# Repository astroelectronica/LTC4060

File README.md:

# LTC4060
Standalone Linear NiMH/NiCd Fast Battery Charger

AE01012060

https://www.analog.com/en/products/ltc4060.html

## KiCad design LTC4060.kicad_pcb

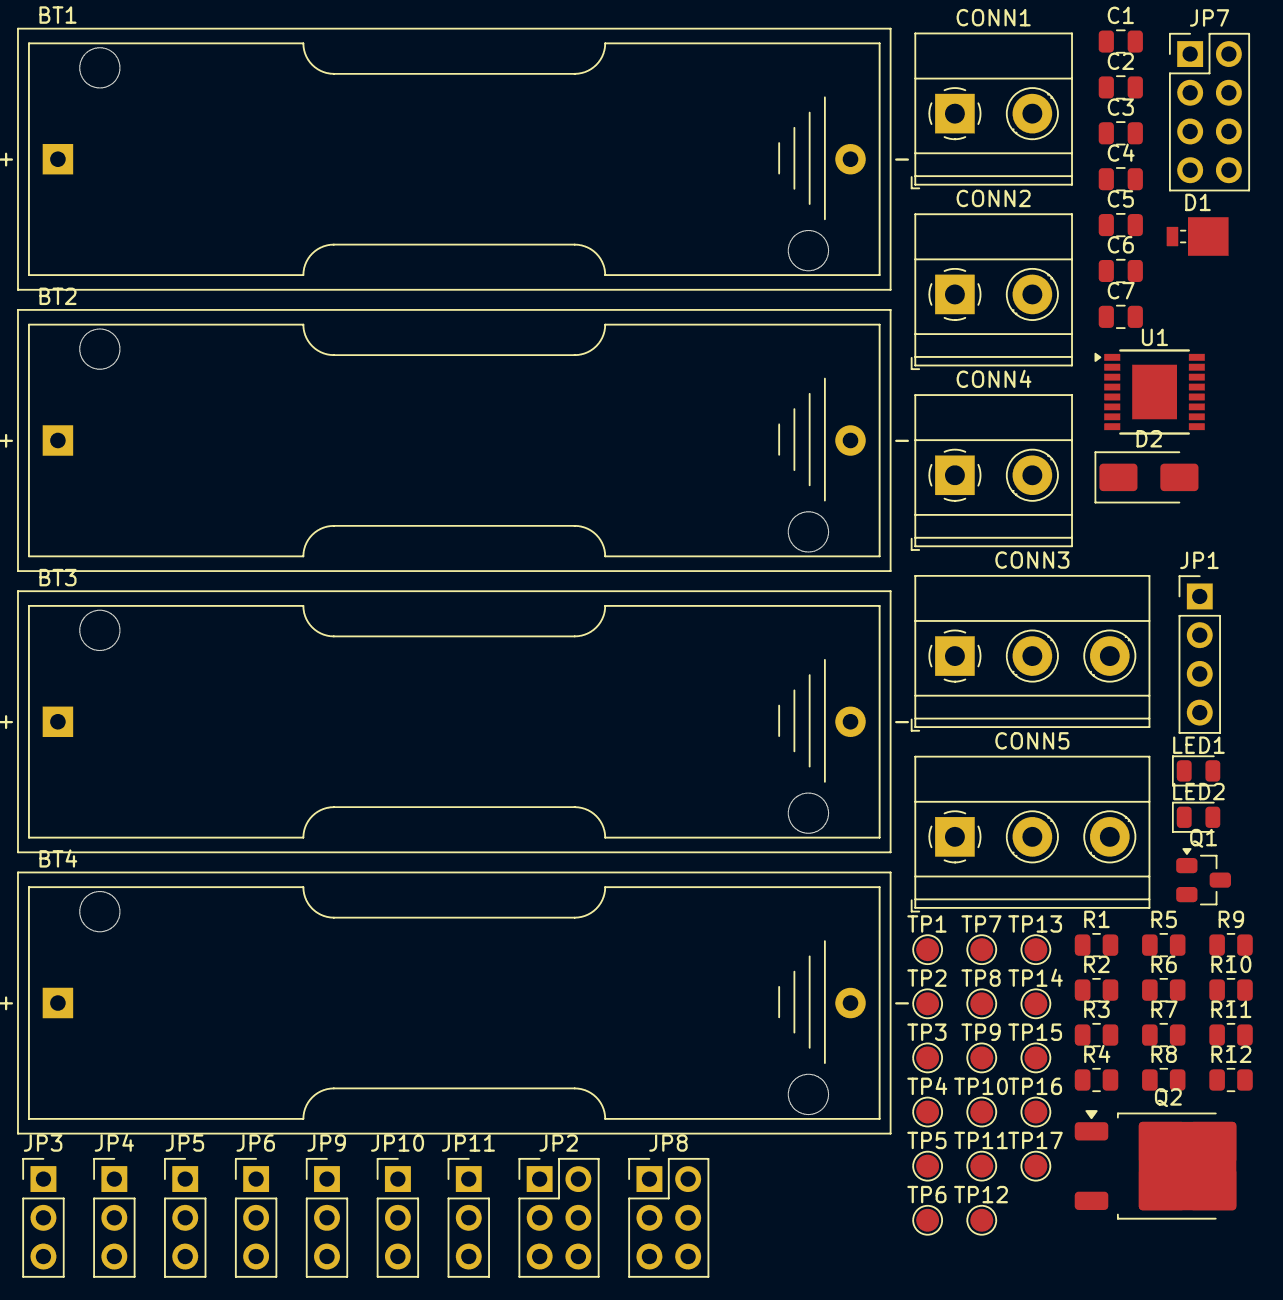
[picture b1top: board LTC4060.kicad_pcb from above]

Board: 2 copper layers, 63 parts (0 on the bottom side), 37 nets, no tracks yet.

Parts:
BT1: CELL1; BatteryHolder_Keystone_2460_1xAA
BT2: CELL2; BatteryHolder_Keystone_2460_1xAA
BT3: CELL3; BatteryHolder_Keystone_2460_1xAA
BT4: CELL4; BatteryHolder_Keystone_2460_1xAA
C1: 1uF; C_0805_2012Metric
C2: 10uF; C_0805_2012Metric
C3: 220pF; C_0805_2012Metric
C4: 150pF; C_0805_2012Metric
C5: 470pF; C_0805_2012Metric
C6: 1200pF; C_0805_2012Metric
C7: 2700pF; C_0805_2012Metric
CONN1: NTC; TerminalBlock_Phoenix_MKDS-1,5-2-5.08_1x02_P5.08mm_Horizont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
CONN2: VIN; TerminalBlock_Phoenix_MKDS-1,5-2-5.08_1x02_P5.08mm_Horizont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
CONN3: TIMER_PROG_EXT; TerminalBlock_Phoenix_MKDS-1,5-3-5.08_1x03_P5.08mm_Horizont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
CONN4: SYST_LOAD; TerminalBlock_Phoenix_MKDS-1,5-2-5.08_1x02_P5.08mm_Horizont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
CONN5: EXT_PNP; TerminalBlock_Phoenix_MKDS-1,5-3-5.08_1x03_P5.08mm_Horizont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
D1: MBRM120LT3; D_Powermite_KA
D2: B220A; D_SMA
JP1: CHRG_CURRENT; PinHeader_1x04_P2.54mm_Vertical
JP2: RECHARGE; PinHeader_2x03_P2.54mm_Vertical
JP3: NTC; PinHeader_1x03_P2.54mm_Vertical
JP4: SEL1; PinHeader_1x03_P2.54mm_Vertical
JP5: SEL0; PinHeader_1x03_P2.54mm_Vertical
JP6: CHEM; PinHeader_1x03_P2.54mm_Vertical
JP7: TIMER; PinHeader_2x04_P2.54mm_Vertical
JP8: EXT_PNP; PinHeader_2x03_P2.54mm_Vertical
JP9: SEL2; PinHeader_1x03_P2.54mm_Vertical
JP10: SEL3; PinHeader_1x03_P2.54mm_Vertical
JP11: SEL4; PinHeader_1x03_P2.54mm_Vertical
LED1: CHRG; LED_0805_2012Metric
LED2: ACPR; LED_0805_2012Metric
Q1: FDN306P; SuperSOT-3
Q2: MJD210T4G; TO-252-2
R1: 931R; R_0805_2012Metric
R2: 2.8K; R_0805_2012Metric
R3, R12: 1R; R_0805_2012Metric
R4: 576R; R_0805_2012Metric
R5: 2.21K; R_0805_2012Metric
R6: 4.42K; R_0805_2012Metric
R7: 68K; R_0805_2012Metric
R8, R10: 330R; R_0805_2012Metric
R9: 390K; R_0805_2012Metric
R11: RSENSE; R_0805_2012Metric
TP1: ARCT; TestPoint_Pad_D1.5mm
TP2: GND; TestPoint_Pad_D1.5mm
TP3: NTC; TestPoint_Pad_D1.5mm
TP4: PAUSE; TestPoint_Pad_D1.5mm
TP5: VIN; TestPoint_Pad_D1.5mm
TP6: SHDN; TestPoint_Pad_D1.5mm
TP7: SEL1; TestPoint_Pad_D1.5mm
TP8: SEL0; TestPoint_Pad_D1.5mm
TP9: CHRG; TestPoint_Pad_D1.5mm
TP10: ACPR; TestPoint_Pad_D1.5mm
TP11: CHEM; TestPoint_Pad_D1.5mm
TP12: TIMER; TestPoint_Pad_D1.5mm
TP13: SENSE; TestPoint_Pad_D1.5mm
TP14: PROG; TestPoint_Pad_D1.5mm
TP15: SYST_LOAD; TestPoint_Pad_D1.5mm
TP16: BATT; TestPoint_Pad_D1.5mm
TP17: DRIVE; TestPoint_Pad_D1.5mm
U1: LTC4060EFE; TSSOP-16-1EP_4.4x5mm_P0.65mm

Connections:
/ARCT: JP2.1, JP2.3, JP2.5, TP1.1, U1.8 (ARCT)
/BATT: BT1.1 (+), CONN5.3, D1.2 (A), JP8.2, Q1.3 (D), R12.1, TP16.1, U1.2 (BAT)
/CHEM: JP6.2, TP11.1, U1.12 (CHEM)
/DRIVE: CONN5.2, JP8.4, TP17.1, U1.1 (DRIVE)
/NTC: CONN1.2, JP3.2, R6.2, TP3.1, U1.11 (NTC)
/PAUSE: R7.1, TP4.1, U1.6 (PAUSE)
/PNP_B: JP8.3, Q2.1 (B)
/PNP_C: JP8.1, Q2.2 (C)
/PNP_E: JP8.5, Q2.3 (E)
/PROG: CONN3.3, JP1.2, R4.1, TP14.1, U1.7 (PROG)
/SEL0: JP5.2, TP8.1, U1.9 (SEL0)
/SEL1: JP4.2, TP7.1, U1.10 (SEL1)
/SENSE: CONN5.1, JP8.6, R11.2, TP13.1, U1.3 (SENSE)
/SYST_LOAD: CONN4.2, D1.1 (K), D2.1 (K), Q1.2 (S), TP15.1
/TIMER: C3.1, CONN3.2, JP7.2, JP7.4, JP7.6, JP7.8, TP12.1, U1.4 (TIMER)
/~ACPR: R10.2, TP10.1, U1.13 (~ACP)
/~CHRG: R8.2, TP9.1, U1.15 (~CHRG)
/~SHDN: R9.2, TP6.1, U1.5 (~SHDN)
GND: BT4.2 (-), C1.2, C2.2, C3.2, C4.1, C5.1, C6.1, C7.1, CONN1.1, CONN2.1, CONN3.1, CONN4.1, JP2.6, JP3.3, JP4.3, JP5.3, JP6.3, JP9.1, JP10.1, JP11.1, R1.1, R2.1, R5.2, R7.2, TP2.1, U1.16 (GND), U1.17 (GNDPAD)
unnamed: BT1.2 (-), JP9.2
unnamed: BT2.1 (+), JP9.3
unnamed: BT2.2 (-), JP10.2
unnamed: BT3.1 (+), JP10.3
unnamed: BT3.2 (-), JP11.2
unnamed: BT4.1 (+), JP11.3
unnamed: C1.1, R3.2
unnamed: C2.1, R12.2
unnamed: JP1.1, R1.2
unnamed: JP1.3, R2.2
unnamed: JP2.4, R4.2, R5.1
unnamed: C4.2, JP7.1
unnamed: C5.2, JP7.3
unnamed: C6.2, JP7.5
unnamed: C7.2, JP7.7
unnamed: LED1.1 (K), R8.1
unnamed: LED2.1 (K), R10.1
VCC: CONN2.2, D2.2 (A), JP2.2, JP4.1, JP5.1, JP6.1, LED1.2 (A), LED2.2 (A), Q1.1 (G), R3.1, R6.1, R9.1, R11.1, TP5.1, U1.14 (VCC)
